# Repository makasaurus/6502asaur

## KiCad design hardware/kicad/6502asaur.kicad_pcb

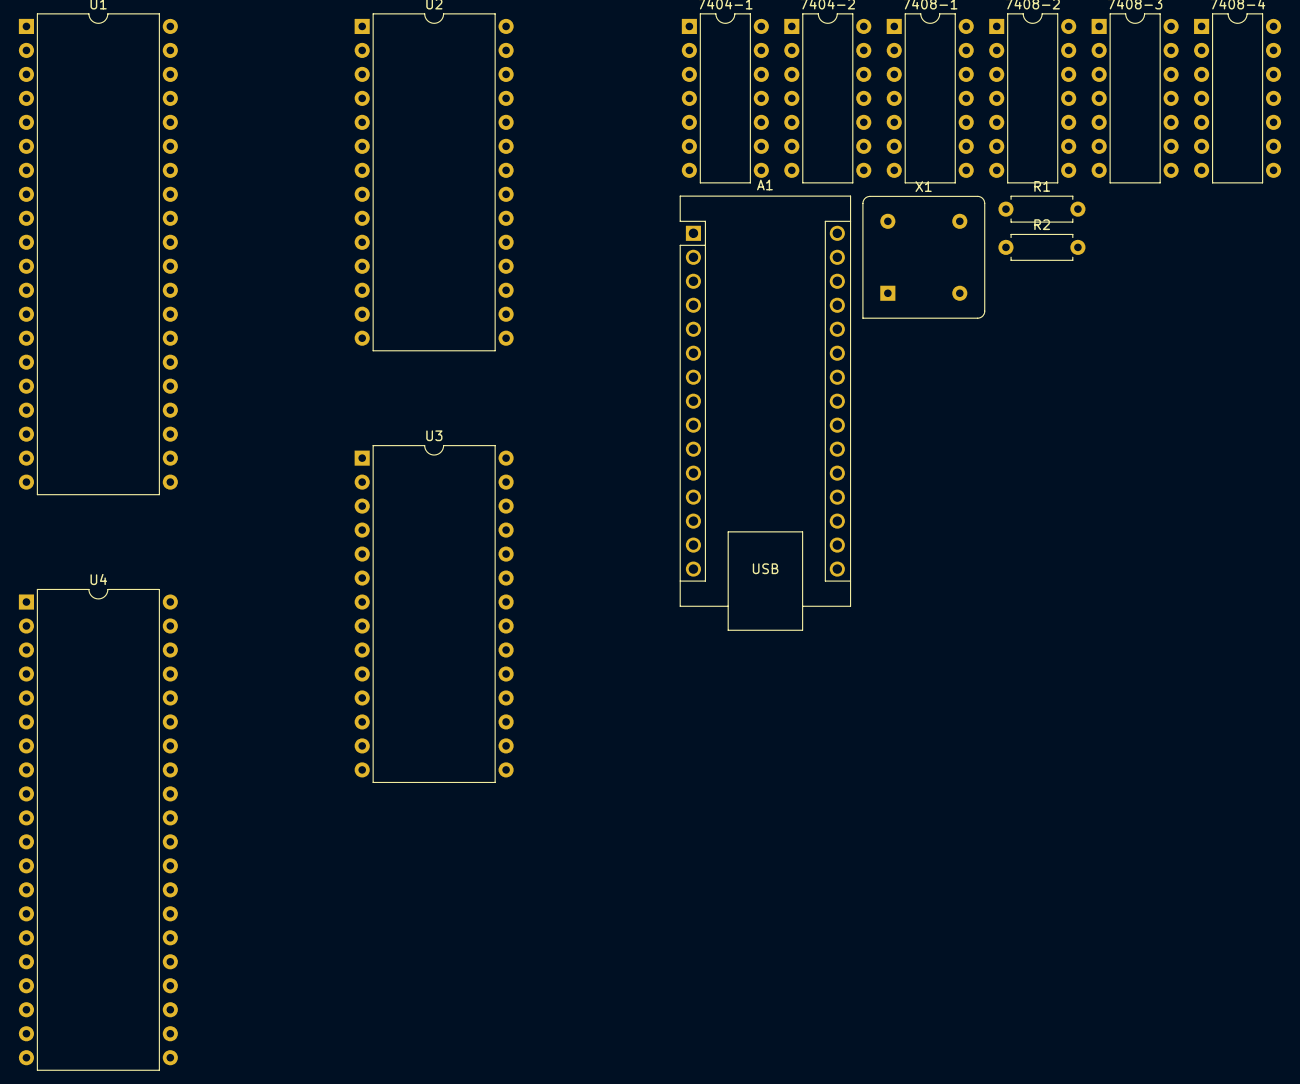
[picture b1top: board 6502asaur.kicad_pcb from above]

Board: 2 copper layers, 14 parts (0 on the bottom side), 57 nets, no tracks yet.

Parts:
7404-1, 7404-2: 74HCT04; DIP-14_W7.62mm
7408-1, 7408-2, 7408-3, 7408-4: 74LS08; DIP-14_W7.62mm
A1: Arduino_Nano_v3.x; Arduino_Nano
R1, R2: 10k; R_Axial_DIN0207_L6.3mm_D2.5mm_P7.62mm_Horizontal
U1: W65C02SxP; DIP-40_W15.24mm
U2: CY62256-70PC; DIP-28_W15.24mm
U3: 28C256; DIP-28_W15.24mm
U4: W65C22SxP; DIP-40_W15.24mm
X1: CXO_DIP8; Oscillator_DIP-8

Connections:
/A0: U1.9 (A0), U2.10 (A0), U3.10 (A0)
/A1: U1.10 (A1), U2.9 (A1), U3.9 (A1)
/A2: U1.11 (A2), U2.8 (A2), U3.8 (A2)
/A3: U1.12 (A3), U2.7 (A3), U3.7 (A3)
/A4: A1.19 (A0), U1.13 (A4), U2.6 (A4), U3.6 (A4)
/A5: A1.20 (A1), U1.14 (A5), U2.5 (A5), U3.5 (A5)
/A6: A1.21 (A2), U1.15 (A6), U2.4 (A6), U3.4 (A6)
/A7: U1.16 (A7), U2.3 (A7), U3.3 (A7)
/A8: U1.17 (A8), U2.25 (A8), U3.25 (A8)
/A9: U1.18 (A9), U2.24 (A9), U3.24 (A9)
/A10: U1.19 (A10), U2.21 (A10), U3.21 (A10)
/A11: U1.20 (A11), U2.23 (A11), U3.23 (A11)
/A12: 7404-1.13, 7408-2.2, 7408-3.2, U1.22 (A12), U2.2 (A12), U3.2 (A12)
/A13: 7404-1.5, 7408-2.12, 7408-3.1, U1.23 (A13), U2.26 (A13), U3.26 (A13)
/A14: 7404-1.3, 7408-1.2, U1.24 (A14), U2.1 (A14), U3.1 (A14)
/A15: 7404-1.1, 7408-1.1, 7408-1.5, U1.25 (A15), U2.22 (~OE)
/D0: U1.33 (D0), U2.11 (Q0), U3.11 (D0), U4.33 (D0)
/D1: U1.32 (D1), U2.12 (Q1), U3.12 (D1), U4.32 (D1)
/D2: U1.31 (D2), U2.13 (Q2), U3.13 (D2), U4.31 (D2)
/D3: U1.30 (D3), U2.15 (Q3), U3.15 (D3), U4.30 (D3)
/D4: U1.29 (D4), U2.16 (Q4), U3.16 (D4), U4.29 (D4)
/D5: U1.28 (D5), U2.17 (Q5), U3.17 (D5), U4.28 (D5)
/D6: U1.27 (D6), U2.18 (Q6), U3.18 (D6), U4.27 (D6)
/D7: U1.26 (D7), U2.19 (Q7), U3.19 (D7), U4.26 (D7)
/PB0: A1.14 (D11), U4.10 (PB0)
/PB1: A1.13 (D10), U4.11 (PB1)
/PB2: A1.12 (D9), U4.12 (PB2)
/PB3: A1.11 (D8), U4.13 (PB3)
/PB4: A1.10 (D7), U4.14 (PB4)
/PB5: A1.9 (D6), U4.15 (PB5)
/PB6: A1.8 (D5), U4.16 (PB6)
/PB7: A1.7 (D4), U4.17 (PB7)
GND: 7404-1.7 (GND), 7404-2.7 (GND), 7408-1.7 (GND), 7408-2.7 (GND), 7408-3.7 (GND), 7408-4.7 (GND), A1.4 (GND), A1.29 (GND), U1.21 (VSS), U2.14 (GND), U3.14 (GND), U4.1 (VSS), X1.4 (GND)
unnamed: 7404-1.2, 7408-3.12
unnamed: 7404-1.4, 7408-1.4
unnamed: 7404-1.6, 7408-1.13, 7408-2.1
unnamed: 7404-1.12, 7408-1.12, 7408-2.13
unnamed: 7404-2.3, 7408-1.3
unnamed: 7404-2.5, 7408-3.6
unnamed: 7404-2.9, 7408-3.11
unnamed: 7404-2.11, 7408-2.8
unnamed: 7404-2.13, 7408-1.8
unnamed: 7408-1.6, 7408-1.9, 7408-2.4, 7408-2.10, 7408-3.4
unnamed: 7408-1.10, 7408-1.11
unnamed: 7408-2.3, 7408-2.5
unnamed: 7408-2.9, 7408-2.11
unnamed: 7408-3.3, 7408-3.5
unnamed: 7408-4.3, A1.6 (D3)
unnamed: R1.1, U1.40 (~RES)
unnamed: R2.1, U1.2 (RDY)
unnamed: U1.34 (R/~W), U2.27 (~WE), U4.22 (R/~W)
unnamed: 7408-3.13, 7408-4.2, U1.37 (ϕ0), U4.25 (ϕ2), X1.5 (OUT)
unnamed: 7404-2.8, U2.20 (~CS)
unnamed: 7404-2.4, U3.20 (~CS)
unnamed: 7404-2.1, 7408-2.6, 7408-4.1, U4.24 (CS1)
unnamed: 7404-2.2, U4.23 (~CS2)
VDD: 7404-1.14 (VCC), 7404-2.14 (VCC), 7408-1.14 (VCC), 7408-2.14 (VCC), 7408-3.14 (VCC), 7408-4.14 (VCC), A1.30 (VIN), R1.2, R2.2, U1.4 (~IRQ), U1.6 (~NMI), U1.8 (VDD), U1.36 (BE), U2.28 (VCC), U3.28 (VCC), U4.20 (VCC), X1.8 (Vcc)
